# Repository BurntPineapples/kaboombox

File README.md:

# KaBoomBox

**An ESP32 wireless firework firing system.** A two-box remote firing system for small
firework and effects shows. A handheld panel with
8 fire buttons and an arming key talks over ESP-NOW to a field box with an 8-channel
relay board and a 12 V battery. The field box checks each igniter for continuity and
reports back, so you can see on the panel which channels are ready before you arm.

Channels can also switch things on and off instead of firing them. One channel can
even switch a 120 V wall outlet for inflatables, lights or a fog machine:
[see the 120 V wall-power channel](#120-v-wall-power-channel-optional).

> [!CAUTION]
> **This fires pyrotechnics. It can hurt or kill people.** It's a hobby project, not a
> certified product, and it comes with no warranty of any kind. Read
> [DISCLAIMER.md](DISCLAIMER.md) before you build or use anything here. You are
> responsible for following the laws where you live. Never bypass the fuse, the arming
> key or the heartbeat auto-disarm.

> [!WARNING]
> **Work in progress.** I'm still actively changing and revising this project. The PCBs,
> printed parts, firmware and docs here are **not final** and may have mistakes or not
> match each other. The current PCB revisions may not have been built or tested yet. If you order boards,
> print parts or build any of this, you do it **at your own risk**: check every file
> yourself first, and expect that things may change after you've built them.

## How it works

```
  PANEL BOX (handheld)                          FIELD BOX (on the ground)
 ┌──────────────────────┐    ESP-NOW 2.4 GHz    ┌───────────────────────────┐
 │ ESP32                │ ── heartbeat/fire ──► │ ESP32                     │
 │ 8 fire buttons + LEDs│ ◄── status/contin. ── │ 8-ch relay board          │
 │ arming key, MODE btn │                       │ continuity sense per ch.  │
 │ 16x2 LCD, link LEDs  │                       │ 12 V SLA ─ fuse ─ relays  │
 │ 4x AA                │                       │          └─► igniters     │
 └──────────────────────┘                       └───────────────────────────┘
```

- The panel sends a heartbeat every 300 ms with the key position. The field box only
  fires while it's hearing a fresh ARMED heartbeat. If the heartbeat is more than 1.5 s
  old it cuts any pulse in progress and refuses new fire commands.
- The field box sends status 4 times a second: continuity for each channel, which relays
  are closed, and its uptime. The panel uses that to light the channel LEDs and to work
  out link quality.
- The two boards are paired by MAC address, and every packet is signed with a secret key
  that only your two boxes have. The field box ignores anything it can't verify,
  including packets someone recorded earlier and plays back.

### Key switch

| Position | What happens |
|---|---|
| Middle: **DISARMED** | Every relay open. MODE opens the settings menu. |
| Left: **ARMED** | Each button fires its own channel (SINGLE), or any button runs your saved sequence (PROGRAM). |
| Right: **ARMED ALL** | Any button starts a 3-2-1 countdown, then fires every ready channel. Turning the key aborts it. |

After power-up the key has to be seen in DISARMED once before it will arm, so the box
can't come up armed if you switch it on with the key in the wrong spot.

### Channel types

Each channel can be set in the menu (saved in flash):

- **FIRE**: pulses the relay for the channel's pulse length (0.1 to 10 s). For igniters.
- **ON/OFF**: press on, press off. For lights or inflatables.
- **HOLD**: relay on only while you hold the button. For fog or similar.

Picking ON/OFF or HOLD also sets that channel's "needs continuity" to NO, so it works
without anything on its sense wire. You can change that back in Channel setup.

### Two ways to use a channel

**12 V pyro (the default).** Channel type FIRE. The relay switches the fused 12 V
firing bus to an igniter on alligator clips. This is what the wiring diagrams and
[`docs/FIELD_WIRING_GUIDE.html`](docs/FIELD_WIRING_GUIDE.html) show. E-matches are
about 1-2 Ω. Steel-wool bench igniters need a 1-2 s pulse.

**120 V wall power (optional).** Channel type ON/OFF or HOLD. One relay switches the
hot wire of an ordinary extension cord, so you can turn on inflatables, lights, a fog
machine or anything else that plugs into a wall. This needs its own wiring and a list
of must-do safety steps: see [120 V wall-power channel](#120-v-wall-power-channel-optional)
before you try it. How the firmware treats that channel:

- **ARMED ALL never turns it on.** Fire-all only launches FIRE channels.
- **Turning the key to DISARMED switches it off**, along with every other ON/OFF and
  HOLD channel.
- **If the radio drops**, the menu's **Link-lost hold** setting decides how long the
  device stays on (default: off at once). HOLD channels always go off at once.
- **It shows "no continuity".** That's expected, because its sense wire is left
  disconnected on purpose.

### Menu (key in DISARMED, press MODE)

btn1 = next, btn2 = back, btn3 = minus, btn4 = plus/start, MODE = back, hold MODE = exit.

1 Link status · 2 Ping test · 3 System check · 4 Continuity · 5 Channel setup ·
6 Link-lost hold · 7 Input test · 8 Info · 9 Reset settings

## What's in here

```
firmware/
  firework_controller/   panel box sketch
  firework_field/        field box sketch
hardware/
  pcb/                   KiCad 10 boards, generator + router scripts, gerber zips
  enclosure/             build123d scripts, STEP/STL files, print/fit test pieces
    plate-source/        the faceplate as drawn in CAD, which the scripts build on
docs/                    wiring sheets (.html, open in a browser)
  images/                photos and wiring diagrams
```

## Parts list

What one complete set uses. The search terms are what to type into Amazon/AliExpress.

### Panel box (handheld)

| Qty | Part | Search for / notes |
|---|---|---|
| 1 | ESP32 38-pin dev board | "ESP32 NodeMCU ESP-32S 38 pin" |
| 1 | ESP32 screw-terminal breakout board | "ESP32 38 pin terminal expansion board". Saves soldering, every wire gets a screw |
| 1 | 16x2 LCD with I2C backpack | "1602 LCD I2C PCF8574". Address 0x27 or 0x3F |
| 1 | 3-position key selector switch, 22 mm | "22mm 3 position key selector switch XB2". Needs **two NO contact blocks** (YJ139-XB2 or similar), one per armed position |
| 8 | Momentary push buttons | Fire buttons. Any panel-mount momentary NO button |
| 1 | Momentary push button | MODE |
| 1 | Toggle switch with safety cover | Power. Mine is a KN3C-101 with the flip-up red cover |
| 8 | LEDs | Channel ready/on |
| 1 + 1 | Green LED, red LED | LINK status |
| 10 | 220 Ω resistors | One per LED |
| 4 | 10 kΩ resistors | Pull-ups for buttons 5-8 |
| 1 | 4x AA battery holder | NiMH rechargeables recommended |
| 1 | Half-size breadboard or perfboard | Resistors, LEDs, power rails |
| 1 | Case | I used a small lockable document case; the printed plate drops into a 9-3/8 x 6-1/4 in opening |
| 8+ | M2 x 6 screws | 4 plate-to-legs, 4 tray-to-legs, more if you screw boards down |

### Field box

| Qty | Part | Search for / notes |
|---|---|---|
| 1 | ESP32 38-pin dev board | Same as above, plus a screw-terminal breakout if you like |
| 1 | ELEGOO 8-channel 5 V relay module | Inputs are active LOW |
| 1 | 12 V SLA battery | Firing power, kept separate from the ESP32 power |
| 1 | Inline fuse holder + 10 A fuse | **The master safety.** No fuse, no firing power |
| 4 | 100 kΩ resistors | Sense pull-ups, channels 1-4 |
| 8 | 10 kΩ resistors | Sense series resistors, one per channel |
| 2-3 | Wago 221 5-slot lever connectors | The shared negative return bus |
| 16 | Alligator clips + wire | Two per channel |
| 1 | USB power source + cable | Powers the field ESP32 (a small power bank works) |
| 1 | Ammo can | About 11 in inside length; the printed floor and front window frame fit it |

**Wire size at the relay board:** the ELEGOO screw terminals take about 16-18 AWG at
most. 14 AWG doesn't fit. If your leads are thicker, use a short 16/18 AWG pigtail or
a ferrule into the terminal.

### Optional: parts for a 120 V wall-power channel

Only if you want one channel to switch a wall device. US 120 V only. Prices are rough
(Nov 2026).

| Qty | Part | Search for / notes | ~$ |
|---|---|---|---|
| 1 | Female cord-end plug, 15 A 125 V, 3-prong | "Leviton 515CV" (515CV-OR is orange). Listed for SJ 16/3 cord | 6 |
| 1 kit | 5x20 mm inline fuse holders (18 AWG, 250 V) + assorted 250 V glass fuses | "5x20mm fuse holder inline screw type with wire combo kit". The XFFCSEC kit has 5 holders and 150 fuses, including 5 A, 6.3 A and 7 A | 10 |
| 1-2 | Old PC power cord (18 AWG, 3-wire), computer end cut off | Reuse one. Or cut a 3 ft 16/3 extension cord in half: that gives you the male and the female end, and you can skip the Leviton | 0-8 |
| 2 | Wago 221 lever nuts | Already in the field box list | - |
| opt | Plug-in GFCI adapter | "plug in GFCI adapter". Skip it if the outlet you use is already GFCI | 12-15 |
| opt | 18 AWG ferrules + crimper | "18 AWG ferrules crimper kit" | - |

A PC cord is usually 18/3, thinner than the 16/3 the Leviton is made for. Tighten its
cord clamp hard and give it a tug. The fuse holder leads go straight into the ELEGOO
screw terminal: twist the strands or crimp a ferrule on. **Don't tin them with
solder**, which loosens under a screw over time.

### Optional

| Qty | Part | Notes |
|---|---|---|
| 2 | PCBs | Replace the breadboards: controller 100 x 84 mm, field 100 x 75 mm. See [PCBs](#pcbs) |
| - | Screw terminals (5.08 mm), 1x19 female headers, 1x10 pin header | For the PCBs |
| - | PETG or ASA filament | For the printed parts |

## Flashing the firmware

1. Install the [Arduino IDE](https://www.arduino.cc/en/software).
2. Add the ESP32 boards: **File → Preferences → Additional boards manager URLs**:
   `https://espressif.github.io/arduino-esp32/package_esp32_index.json`
   then **Tools → Board → Boards Manager**, search "esp32" and install **esp32 by
   Espressif Systems**. The sketches handle both the 2.x and 3.x cores.
3. **Sketch → Include Library → Manage Libraries**, install **LiquidCrystal I2C** by
   Frank de Brabander (panel box only).
4. Board: **ESP32 Dev Module**. Open `firmware/firework_controller/firework_controller.ino`,
   upload it to the panel ESP32. Open `firmware/firework_field/firework_field.ino` and
   upload it to the field ESP32.

### Your secret key (do this first)

The boxes sign every message with a key only they know, so nobody else can make a fake
panel that your field box would obey. The sketches won't compile until you make one.

1. Copy `secrets.example.h` to `secrets.h` in `firmware/firework_controller/`.
2. Make a random key. In a terminal:

   ```bash
   python -c "import secrets; print(', '.join('0x%02X' % b for b in secrets.token_bytes(32)))"
   ```

   Paste the 32 numbers into `secrets.h` and set `KABOOM_KEY_IS_PLACEHOLDER` to `0`.
3. Copy that same `secrets.h` into `firmware/firework_field/`. Both boxes need the
   **same** key.

Keep `secrets.h` to yourself. It's in `.gitignore`, so it won't be uploaded if you fork
this repo. If the two boxes have different keys they won't link, and the LCD says
`FW/SECRET DIFFER`.

### Pairing the two boards

The MAC addresses in the sketches are for my boards. Yours will be different.

1. Flash both sketches (with your `secrets.h`) and open **Serial Monitor at 115200 baud**.
2. Each board prints its own MAC at boot (`MY MAC - paste into ...`).
3. Put the **field** board's MAC into `FIELD_MAC` in `firework_controller.ino`.
4. Put the **controller** board's MAC into `CONTROLLER_MAC` in `firework_field.ino`.
5. Re-flash both. The green link LED should come on.

`44:1D:64:BD:75:50` becomes `{0x44, 0x1D, 0x64, 0xBD, 0x75, 0x50}`.

### Settings you might change

| Setting | File | Default | What it does |
|---|---|---|---|
| `FIELD_MAC` | firework_controller.ino | my board | MAC of your field box |
| `CONTROLLER_MAC` | firework_field.ino | my board | MAC of your panel box |
| `LCD_ADDR` | firework_controller.ino | `0x27` | Try `0x3F` if the screen stays blank (and turn the contrast pot) |
| `USE_LONG_RANGE` | **both** | `0` | `1` turns on ESP32 long-range mode. Must match on both boards |
| `MAX_PULSE_MS` | firework_field.ino | `10000` | Hard cap on any one pulse, whatever the panel asks for |
| `HEARTBEAT_TIMEOUT` | firework_field.ino | `1500` | Field disarms after this many ms without a heartbeat. Don't raise it |

Everything else (channel types, pulse lengths, continuity check, link-lost hold, the
saved sequence) is set from the menu on the panel and stored in flash.

If you change the message format, bump `PROTO_VER` in both sketches. Boards with a
different `PROTO_VER` ignore each other instead of misfiring. Version 3 (`0xA3`) added
the signing, so a v2 box won't talk to a v3 box: flash both.

## Wiring

The pin numbers in these diagrams match the sketches. The step-by-step sheets in
[`docs/`](#docs) go wire by wire.

### 120 V wall-power channel (optional)

> [!CAUTION]
> **Wall power can kill you, and a mistake here can put 120 V on the igniter clips or
> the ESP32.** Only do this if you're comfortable wiring mains, and go through every
> step in the checklist below. US 120 V only: 230 V countries need different plugs,
> wire colours and fuse values. If you're unsure, use a ready-made relay outlet box
> that takes a low-voltage control input instead.

**How it works:** the relay switches only the **hot** wire of an ordinary cord. Neutral
and ground go straight through on Wagos and never touch the relay board. The example
uses channel 8.

| From | Through | To |
|---|---|---|
| Wall plug **HOT** (narrow blade, usually black) | Inline fuse holder, 250 V, 5 A slow-blow | Relay **COM8** |
| Relay **NO8** | | Female plug **HOT** (brass screw) |
| Wall plug **NEUTRAL** (wide blade, usually white) | Wago | Female plug **NEUTRAL** (silver screw) |
| Wall plug **GROUND** (green) | Wago | Female plug **GROUND** (green screw) |
| Channel 8 continuity-sense wire | | **Nothing.** Leave that sense terminal empty |

Before you cut anything, check with a continuity meter which wire goes to the narrow
blade. Don't trust the colours alone.

In the menu, set channel 8 to **ON/OFF** (or HOLD) under **Channel setup**. Then, with
the key in ARMED, button 8 turns the outlet on and off.

**Must-do checklist** (every one of these, every build):

1. **Remove CH8's COM jumper.** All the other COMs are tied to the 12 V firing bus. If
   CH8's COM stays jumpered, 120 V lands on every channel's igniter clips.
2. **Disconnect CH8's sense wire** (on a breadboard, take out its 10 kΩ series
   resistor). Through that resistor 120 V would reach the ESP32 pin, kill the board and
   make the whole low-voltage side live. The 10 kΩ only protects against 12 V.
3. **Unplugging the 12 V battery doesn't make shared wiring safe.** Steps 1 and 2 are
   needed even if 12 V and 120 V are never connected at the same time.
4. **Switch the hot only**, never the neutral.
5. **The fuse must be rated 250 V.** Don't reuse the 12 V system's automotive blade
   fuse: blade fuses are rated 32 V and can keep arcing on wall power instead of
   breaking the circuit.
6. **Fuse size:** start at 5 A. If a fast-blow pops when a blower motor starts, step up
   to 6.3 A, then 7 A. Never go above 8 A on 18 AWG cord. A fuse that blows while the
   device is already running means a real fault: unplug it and find the problem.
7. **Load limit about 5 A / 600 W.** Fine for inflatables, lights and fog machines. No
   heaters or big motors.
8. **Strain relief:** two zip ties pulled tight around each cord just inside the box.
   Smooth the entry hole, or wrap the cord in tape where it passes through. Tug on the
   cord: the screw terminals must not feel the pull.
9. **Keep mains wires on one side of the box**, zip-tied, away from the ESP32 and the
   12 V wiring. The ELEGOO board has bare solder joints on the back, so mount it on
   standoffs with tape or plastic under the mains channels. If any part of the box is
   metal, bond it to the green ground wire.
10. **Label the channel "120V"** on the box so nobody clips an igniter to it.
11. **Use a GFCI outlet** (the kind with TEST/RESET buttons) or a plug-in GFCI adapter,
    especially with people around.
12. **Always unplug the wall cord before you open the box.** Keep the lid shut while
    it's in use.
13. **First power-up check, with the wall cord still unplugged**, using a meter:
    - wall plug HOT to female plug HOT reads open;
    - turn channel 8 on from the panel: now it beeps;
    - wall plug HOT to the 12 V bus, and to GND, reads open with the relay off and on.

Don't bypass the 10 A firing fuse, the shared ground, the 10 kΩ series resistors or
the arming key on the 12 V channels to make room for this. They stay exactly as they are.

## Pin maps

### Panel box (`firework_controller.ino`)

| Function | GPIO |
|---|---|
| Fire buttons 1-8 (to GND) | 13, 14, 25, 26, 34, 35, 36, 39 (34-39 need an external 10 k pull-up to 3V3) |
| Channel LEDs 1-8 (220 Ω to GND) | 4, 19, 21, 22, 23, 18, 32, 33 |
| Key ARMED / ARMED ALL (key common to 3V3) | 17 / 27 |
| MODE button (to GND) | 15 |
| Link LED green / red | 2 / 12 |
| LCD SDA / SCL (LCD VCC to 5 V) | 16 / 5 |

### Field box (`firework_field.ino`)

| Channel | 1 | 2 | 3 | 4 | 5 | 6 | 7 | 8 |
|---|---|---|---|---|---|---|---|---|
| Relay IN (active LOW) | 26 | 27 | 14 | 13 | 25 | 33 | 32 | 16 |
| Continuity sense | 36 | 39 | 34 | 35 | 4 | 17 | 18 | 19 |

Each sense pin connects through a 10 k series resistor to that relay's NO terminal
(where the igniter's hot lead lands). Channels 1-4 need a 100 k pull-up to 3V3; 5-8 use
the ESP32's internal pull-up. An igniter in place pulls the pin LOW.

## PCBs

Both boards are generated by Python scripts that run inside KiCad's own Python, then
auto-routed with [freerouting](https://github.com/freerouting/freerouting).

| Board | Size | Files |
|---|---|---|
| Panel (controller) | 100 x 84 mm | `hardware/pcb/controller/` · `controller-gerbers.zip` |
| Field | 100 x 75 mm | `hardware/pcb/field/` · `field-gerbers.zip` |

**Ordering:** upload the gerber zip at [jlcpcb.com](https://jlcpcb.com) (or any other
fab). The defaults are fine: 2 layers, 1.6 mm, HASL.

**Before you order, measure your ESP32.** The boards assume the two pin rows are
25.4 mm (1.0") apart. Some dev boards are 22.86 mm (0.9"). If yours is different,
change `ESP_ROW_SPACING` at the top of the generator script and rebuild. Print
`field/field-paper-check-1to1.pdf` at 100% scale and set your parts on it to check
the fit.

**Rebuilding** (needs [KiCad 10](https://www.kicad.org/), Java and freerouting):

```
cd hardware/pcb
"C:\Program Files\KiCad\10.0\bin\python.exe" generate_controller.py
"C:\Program Files\KiCad\10.0\bin\python.exe" route_controller.py path\to\freerouting.jar
```

The scripts point to my KiCad install at `E:\KiCad`. Change `FP_ROOT` at the top of each
generator to your KiCad footprint folder. Running a generator **wipes the routing** on
that board, so always run the router after it. Then export gerbers from KiCad
(File → Fabrication Outputs) and zip them.

## Enclosure

The panel is a printed 9.2 x 6.1 in plate with an angled LCD pod, legs and an internal
parts tray, made to drop into a box with a 9-3/8 x 6-1/4 in opening. The field parts are a floor plate and a front window
frame for an ammo can.

### What to print

All in `hardware/enclosure/`. Print the `_test` pieces first: they're thin slices of the
real part, take a few minutes, and tell you if the fit is right before you spend hours
on the full print.

| File | Part | How to print |
|---|---|---|
| [`controller_full.stl`](hardware/enclosure/controller_full.stl) | Panel faceplate (1/8 in thick) with the 30° LCD pod, M2 counterbores in the corners | Plate bottom on the bed (as exported) |
| [`legs_print.stl`](hardware/enclosure/legs_print.stl) | Four corner legs + floor ring, one piece | As exported, floor ring on the bed |
| [`tray_print.stl`](hardware/enclosure/tray_print.stl) | Parts tray: breadboard corral, ESP32 corners, battery cradle | Slab down, no supports |
| [`field_floor.stl`](hardware/enclosure/field_floor.stl) | Insulating floor plate for the ammo can | Skirt up (top face on the bed), no supports |
| [`field_prop.stl`](hardware/enclosure/field_prop.stl) | Front window frame that clamps on the can rim; wires pass through it | Standing on its end with a brim, no supports |

Fit tests:

| File | Checks |
|---|---|
| [`controller_plate_test.stl`](hardware/enclosure/controller_plate_test.stl) | 1.5 mm slice of the faceplate: outline, every hole, LCD opening |
| [`legs_test.stl`](hardware/enclosure/legs_test.stl) | Floor ring and the bottom 15 mm of the legs: footprint on the box floor |
| [`field_floor_test.stl`](hardware/enclosure/field_floor_test.stl) | Floor outline in the can |
| [`field_prop_test.stl`](hardware/enclosure/field_prop_test.stl) | Rim and lid grooves of the window frame |

Not for printing: `plate-source/Controller.stl` and `plate-source/Controller_9.200x6.100.stl`
are the faceplate as drawn in CAD, before and after `shrink_plate.py`. The scripts build
`controller_full` from them.

Every printable part also has a `.step` file for CAD. PETG or ASA hold up better outdoors
than PLA, which can soften in a hot car or in direct sun.

To regenerate them you need Python 3 and build123d:

```
pip install build123d
cd hardware/enclosure
python legs_step.py
```

A few scripts copy their output into my CAD folder (`E:\InventorProjects\...`)
or read the plate STL from there. If you don't have that folder, delete those
`shutil.copy` lines and point `SRC` at the matching file in `plate-source/`.
To rebuild the faceplate, run `lcd_pod_step.py` first, then `plate_test.py`.

## Docs

Open these in a browser:

- [`docs/CONTROLLER_WIRING.html`](docs/CONTROLLER_WIRING.html): panel box wiring, step by step
- [`docs/FIELD_WIRING_GUIDE.html`](docs/FIELD_WIRING_GUIDE.html): field box power and clip wiring, plus the optional 120 V wall-power channel
- [`docs/SCHEMATIC_field.html`](docs/SCHEMATIC_field.html): field box schematic

## Before every use

- Test with **no pyrotechnics connected**. Put an LED or test lamp across each channel's
  clips and fire every channel.
- Run **System check** from the menu. It should say PASS.
- Turn the key to DISARMED and **pull the fuse** before you walk up to the field box.
  Connect igniters last, fuse in last, and walk away before you arm.
- If something doesn't fire, disarm, pull the fuse, and wait before you approach.

If you have a 120 V wall-power channel:

- Its channel is still set to **ON/OFF** or **HOLD** (not FIRE), and it's labelled "120V".
- Its **COM is not jumpered** to the 12 V bus and its **sense wire is disconnected**.
- The wall cord is **unplugged** whenever the box is open. Lid shut, then plug in.
- It's plugged into a **GFCI** outlet or adapter, and the cord's strain relief holds
  when you tug it.

## License

- Firmware and scripts: [MIT](LICENSE)
- Hardware designs (PCB, enclosure, STL/STEP files) and docs:
  [CERN-OHL-P v2](LICENSE-HARDWARE)

Both come with no warranty. See [DISCLAIMER.md](DISCLAIMER.md) as well. By using
anything in this repo you accept that you do so entirely at your own risk.

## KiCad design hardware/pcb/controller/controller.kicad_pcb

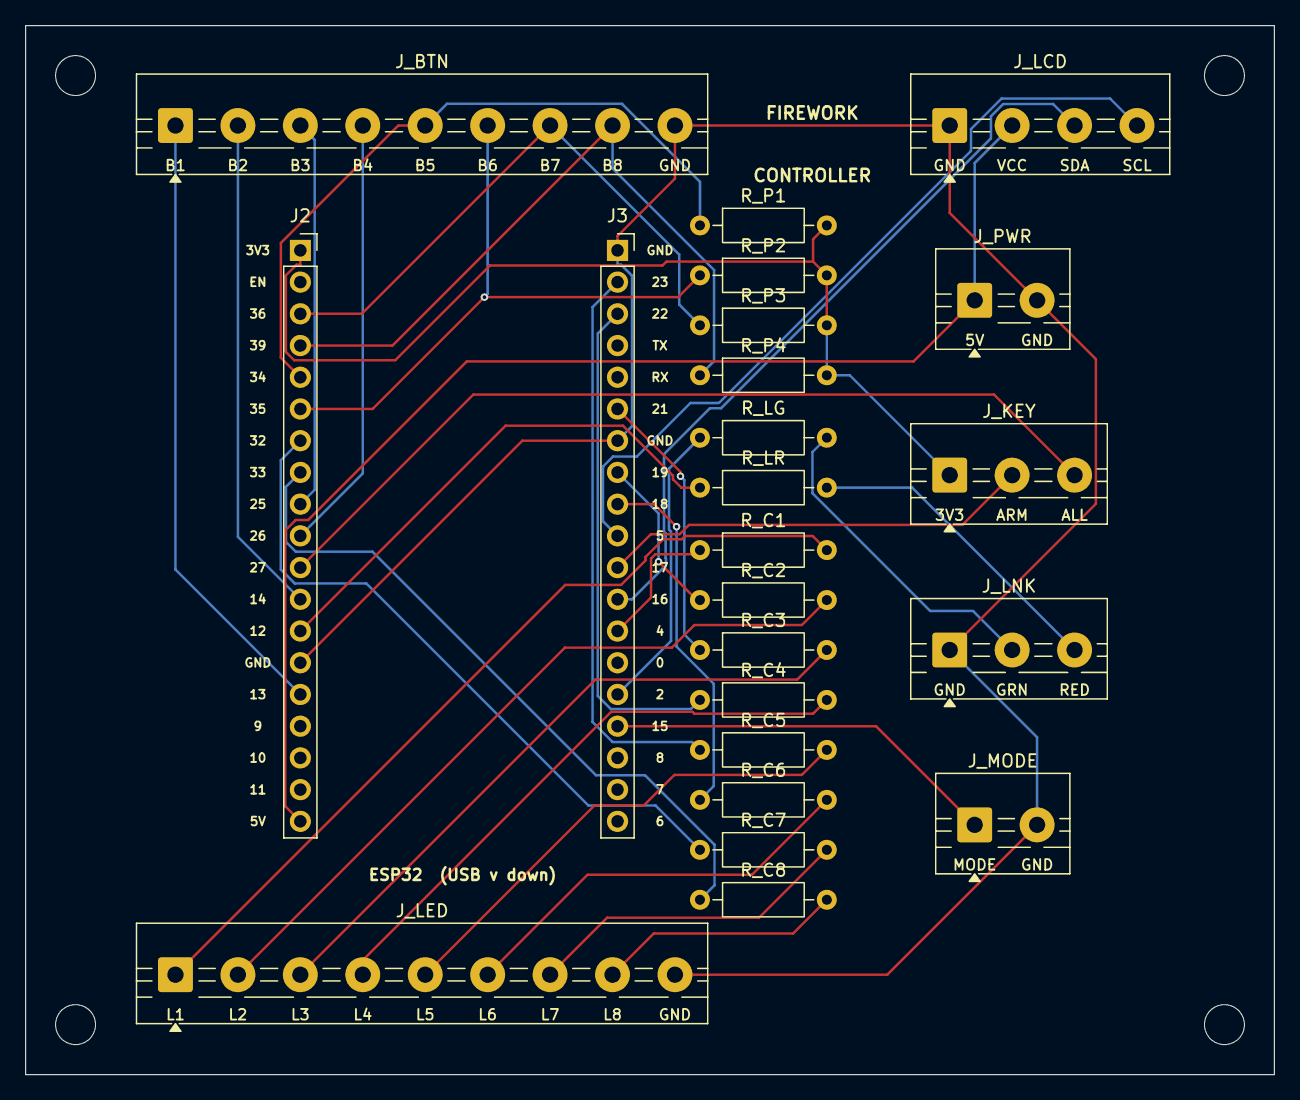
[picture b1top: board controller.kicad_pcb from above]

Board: 2 copper layers, 100.0 x 84.0 mm, 27 parts (0 on the bottom side), 36 nets.

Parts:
H1, H2, H3, H4: M3; MountingHole_3.2mm_M3
J2: ESP32 left; PinSocket_1x19_P2.54mm_Vertical
J3: ESP32 right; PinSocket_1x19_P2.54mm_Vertical
J_BTN: fire buttons 1-8 +GND; TerminalBlock_MaiXu_MX126-5.0-09P_1x09_P5.00mm
J_KEY: key switch; TerminalBlock_MaiXu_MX126-5.0-03P_1x03_P5.00mm
J_LCD: 16x2 I2C LCD; TerminalBlock_MaiXu_MX126-5.0-04P_1x04_P5.00mm
J_LED: channel LEDs 1-8 +GND; TerminalBlock_MaiXu_MX126-5.0-09P_1x09_P5.00mm
J_LNK: link LEDs G/R +GND; TerminalBlock_MaiXu_MX126-5.0-03P_1x03_P5.00mm
J_MODE: mode button; TerminalBlock_MaiXu_MX126-5.0-02P_1x02_P5.00mm
J_PWR: 5V power in; TerminalBlock_MaiXu_MX126-5.0-02P_1x02_P5.00mm
R_C1, R_C2, R_C3, R_C4, R_C5, R_C6, R_C7, R_C8: 220; R_Axial_DIN0207_L6.3mm_D2.5mm_P10.16mm_Horizontal
R_LG: 220; R_Axial_DIN0207_L6.3mm_D2.5mm_P10.16mm_Horizontal
R_LR: 220; R_Axial_DIN0207_L6.3mm_D2.5mm_P10.16mm_Horizontal
R_P1, R_P2, R_P3, R_P4: 10k; R_Axial_DIN0207_L6.3mm_D2.5mm_P10.16mm_Horizontal

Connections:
3V3: J2.1, J_KEY.1, R_P1.2, R_P2.2, R_P3.2, R_P4.2
5V: J2.19, J_LCD.2, J_PWR.1
BTN1: J2.15, J_BTN.1
BTN2: J2.12, J_BTN.2
BTN3: J2.9, J_BTN.3
BTN4: J2.10, J_BTN.4
BTN5: J2.5, J_BTN.5, R_P1.1
BTN6: J2.6, J_BTN.6, R_P2.1
BTN7: J2.3, J_BTN.7, R_P3.1
BTN8: J2.4, J_BTN.8, R_P4.1
GND: J2.14, J3.1, J3.7, J_BTN.9, J_LCD.1, J_LED.9, J_LNK.1, J_MODE.2, J_PWR.2
KEY_ALL: J2.11, J_KEY.3
KEY_ARM: J3.11, J_KEY.2
LCD_SCL: J3.10, J_LCD.4
LCD_SDA: J3.12, J_LCD.3
LED1: J3.13, R_C1.1
LED1_A: J_LED.1, R_C1.2
LED2: J3.8, R_C2.1
LED2_A: J_LED.2, R_C2.2
LED3: J3.6, R_C3.1
LED3_A: J_LED.3, R_C3.2
LED4: J3.3, R_C4.1
LED4_A: J_LED.4, R_C4.2
LED5: J3.2, R_C5.1
LED5_A: J_LED.5, R_C5.2
LED6: J3.9, R_C6.1
LED6_A: J_LED.6, R_C6.2
LED7: J2.7, R_C7.1
LED7_A: J_LED.7, R_C7.2
LED8: J2.8, R_C8.1
LED8_A: J_LED.8, R_C8.2
LED_FAIL: J2.13, R_LR.1
LED_PASS: J3.15, R_LG.1
LNKG_A: J_LNK.2, R_LG.2
LNKR_A: J_LNK.3, R_LR.2
MODE_BTN: J3.16, J_MODE.1

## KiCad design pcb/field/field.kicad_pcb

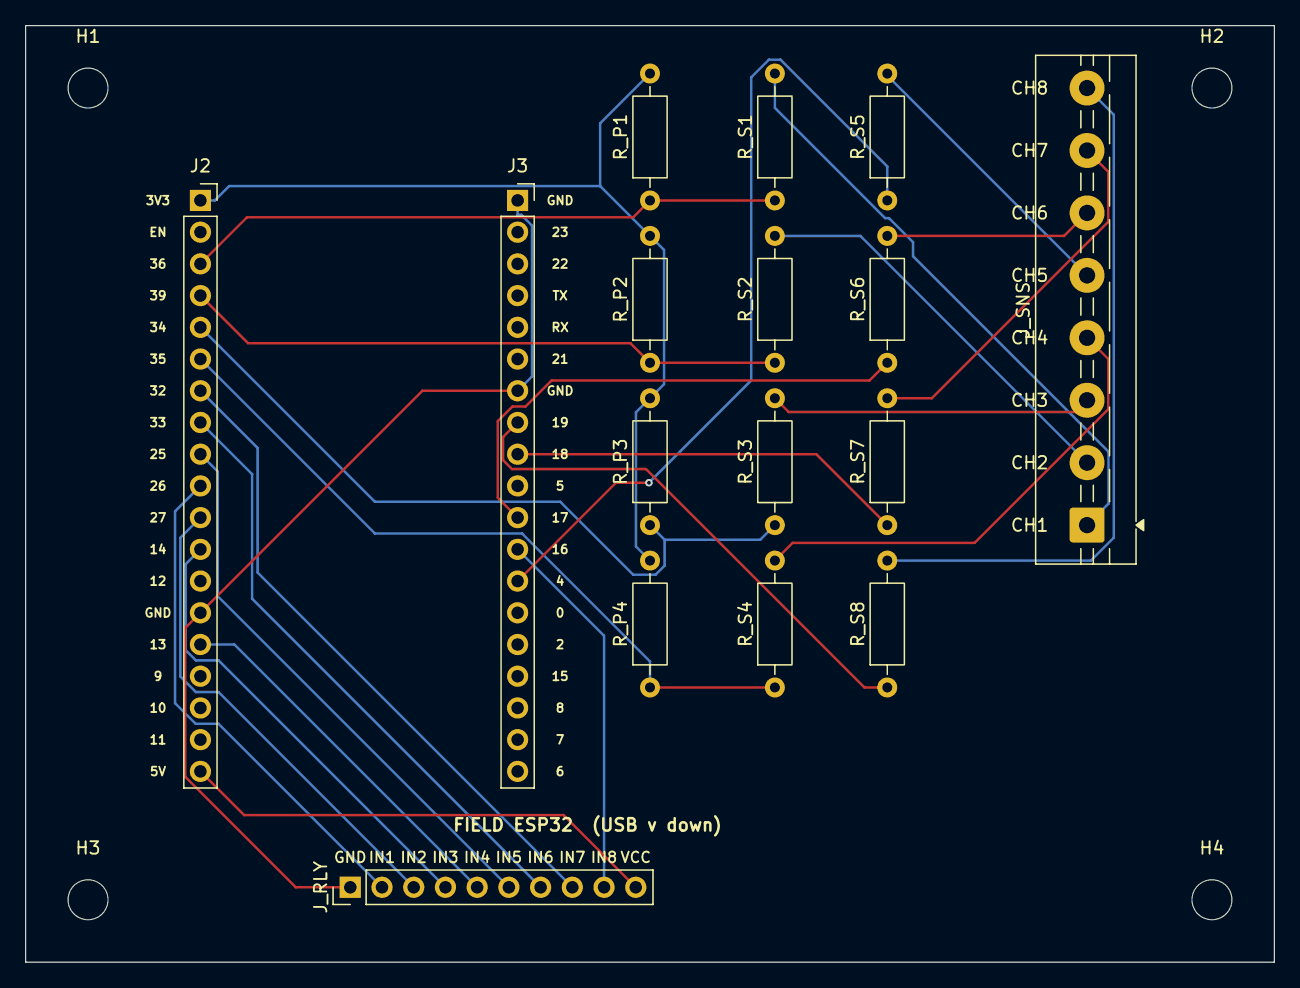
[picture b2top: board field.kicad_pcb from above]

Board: 2 copper layers, 100.0 x 75.0 mm, 20 parts (0 on the bottom side), 27 nets.

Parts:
H1, H2, H3, H4: M3; MountingHole_3.2mm_M3
J2: ESP32 left; PinSocket_1x19_P2.54mm_Vertical
J3: ESP32 right; PinSocket_1x19_P2.54mm_Vertical
J_RLY: to relay module; PinHeader_1x10_P2.54mm_Vertical
J_SNS: sense taps to relay NO; TerminalBlock_MaiXu_MX126-5.0-08P_1x08_P5.00mm
R_P1, R_P2, R_P3, R_P4: 100k; R_Axial_DIN0207_L6.3mm_D2.5mm_P10.16mm_Horizontal
R_S1, R_S2, R_S3, R_S4, R_S5, R_S6, R_S7, R_S8: 10k; R_Axial_DIN0207_L6.3mm_D2.5mm_P10.16mm_Horizontal

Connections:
3V3: J2.1, R_P1.2, R_P2.2, R_P3.2, R_P4.2
5V: J2.19, J_RLY.10
GND: J2.14, J3.1, J3.7, J_RLY.1
IN1: J2.10, J_RLY.2
IN2: J2.11, J_RLY.3
IN3: J2.12, J_RLY.4
IN4: J2.15, J_RLY.5
IN5: J2.9, J_RLY.6
IN6: J2.8, J_RLY.7
IN7: J2.7, J_RLY.8
IN8: J3.12, J_RLY.9
NO1: J_SNS.1, R_S1.2
NO2: J_SNS.2, R_S2.2
NO3: J_SNS.3, R_S3.2
NO4: J_SNS.4, R_S4.2
NO5: J_SNS.5, R_S5.2
NO6: J_SNS.6, R_S6.2
NO7: J_SNS.7, R_S7.2
NO8: J_SNS.8, R_S8.2
SENSE1: J2.3, R_P1.1, R_S1.1
SENSE2: J2.4, R_P2.1, R_S2.1
SENSE3: J2.5, R_P3.1, R_S3.1
SENSE4: J2.6, R_P4.1, R_S4.1
SENSE5: J3.13, R_S5.1
SENSE6: J3.11, R_S6.1
SENSE7: J3.9, R_S7.1
SENSE8: J3.8, R_S8.1

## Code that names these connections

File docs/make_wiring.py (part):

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    return int(re.search(r"const int " + name + r"\s*=\s*(\d+)", src).group(1))

BTN, LED = arr(ctrl, "BTN_PIN"), arr(ctrl, "LED_PIN")
KEY_A, KEY_ALL, MODE = const(ctrl, "PIN_KEY_ARMED"), const(ctrl, "PIN_KEY_ALL"), const(ctrl, "PIN_MODE_BTN")
LG, LR, SDA, SCL = (const(ctrl, n) for n in ("PIN_LED_PASS", "PIN_LED_FAIL", "PIN_LCD_SDA", "PIN_LCD_SCL"))
RELAY, SENSE = arr(fld, "RELAY_PIN"), arr(fld, "SENSE_PIN")

INK, MUTED, SIG, PWR, GND, SNS, BOX = "#e6edf3", "#9da7b3", "#58a6ff", "#ff6b6b", "#c9d1d9", "#e3b341", "#161b22"
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left = [(f"Fire button {i+1}", f"GPIO {p}", "other leg → GND" + (" · 10k pull-up to 3V3" if p >= 34 else "")) for i, p in enumerate(BTN)]
left += [("MODE button", f"GPIO {MODE}", "other leg → GND"),
         ("Key: ARMED contact", f"GPIO {KEY_A}", "key common → 3V3"),
         ("Key: ARMED ALL contact", f"GPIO {KEY_ALL}", "key common → 3V3")]
right = [(f"Channel LED {i+1}", f"GPIO {p}", "220Ω", "− leg → GND") for i, p in enumerate(LED)]
right += [("LINK LED green", f"GPIO {LG}", "220Ω", "− leg → GND"), ("LINK LED red", f"GPIO {LR}", "220Ω", "− leg → GND"),
          ("LCD SDA", f"GPIO {SDA}", "", "I2C backpack"), ("LCD SCL", f"GPIO {SCL}", "", "I2C backpack")]
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

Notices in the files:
docs/make_wiring.py:
Copyright (c) 2026 Burnt pineapples
SPDX-License-Identifier: MIT
